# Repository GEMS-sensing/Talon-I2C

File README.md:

<!--  -->

# Talon-I2C
Talon daughterboard for [Flight data logger](https://github.com/GEMS-sensing/DFM_-_Flight?tab=readme-ov-file). Designed to interface with [Kestrel](https://github.com/GEMS-sensing/Project-Kestrel) main board. This board is designed to provide data logger with support to interface with I2C based sensors - a common interface for open source sensors.

# Repo Roadmap
#### [Documents](Documents/) 

General document and image storage for repo and README

#### [Hardware](Hardware/)

Current board files (Eagle), Bill of Materials (BoM), and other design documents

#### [Production](Production/)

Contains the various Gerber and pick and place files required to have the Printed Circuit Boards (PCBs) manufactured or populated 

#### [Software](Software/)

The software associated with the piece of hardware, this is usually diagnostic software used for verifying or investigating the hardware

<!-- #### [Mechanical](Mechanical/)

Mechanical design files and assembly documents -->

<!-- #### [Testing](Testing/)

Scripts and results from the testing process and development process. Contains more detailed information about documented issues among other testing. 
 -->

## Overview
* **Type:** Talon
* **Interfaces:** SDI-12
* **Release Version:** v2.1 - 2022/04/25

<!--  -->

## Features
### On-Board
* I2C ports (x4)
	* Isolated I2C bus for each port with line driver to deal with long, high capacitance sensor cables
* Port level current limit
	* Custom designed automatic current limit 
	* support for current and voltage measurement for each port
* Data and power control for each port
* Internal and external isolated I2C buses 
* EEPROM with UUID built in - can store additional values defined by firmware to track offsets, etc
* ESD protected inputs

<!-- ### Interface
* I<sup>2</sup>C
* M12 circular connector  -->

<!-- <picture>
  <source media="(prefers-color-scheme: dark)" srcset="Documents/Pinout_LIGHT.png">
  
</picture> -->

<!-- ## Specifications
* **Voltage - Supply:** 3.3V
* **Voltage - Logic:** 3.3V
* **Input Current (Avg, 1s period): 30.95&mu;A @ 3.3V**
* **Input Current (Avg, 5s period): 107.43&mu;A @ 3.3V**
* **Input Current (Max): 0.45mA @ 3.3V**

#### Sensor
**Temperature** [^1]
* Range: -40 ~ 125°C 
* Accuracy: &plusmn; 0.2°C
* Repeatability: &plusmn; 0.04°C

**Pressure** [^2]
* Range: 300 ~ 1200 hPa  
* Accuracy: &plusmn; 1 hPa
* Repeatability: &plusmn; 0.06 hPa

**Humidity** [^1]
* Range: 0 ~ 100%
* Accuracy: &plusmn; 2%
* Repeatability: 0.08%

[^1]: [SHT31 Datasheet](https://sensirion.com/media/documents/213E6A3B/63A5A569/Datasheet_SHT3x_DIS.pdf)
[^2]: [DPS368 Datasheet](https://www.infineon.com/dgdl/Infineon-DPS368-DS-v01_00-EN.pdf?fileId=5546d46269e1c019016a0c45105d4b40) -->

<!-- ## Version History

`v0.0` - Initial primal version with screw terminal

`v0.1` - Initial 'hard mount' version, using M12 connector

`v1.0` - Removed pullup select[^3], added logic level buffer and voltage reg on input

`v1.1` - Moved via away from connector pads to prevent bridging when soldering 

`v2.0` - Fixed issue with address select jumper[^3] -->

<!-- ## Jumper Settings 

> [!IMPORTANT]
> Jumper settings valid for version `v2.0` and beyond[^3]

[^3]: See Errata

**Configuration Jumpers**
| Jumper | Purpose | Open | Closed | Default | 
| ------ | ------- | ---------- | ---------- | ----- | 
| `JP1` | I<sup>2</sup>C Address Select | Base Address<sup>&dagger;</sup> | Alt Address<sup>&Dagger;</sup> | Open |

&dagger; SHT31 = `0x44`, DPS368 = `0x76`

&Dagger; SHT31 = `0x44`, DPS368 = `0x77`
 -->

## Known Issues/Errata

None
<!-- #### Solder Jumper Stencil

**Version Affected:** All

**Issue:** Solar input does not support very low impedance sources (e.g. lead acid battery) - see details in issue [#20](https://github.com/GEMS-sensing/Project-Kestrel/issues/20)

**Workaround:** 

* Avoid use of low impedance batteries for input
* Include series impedance to prevent current spikes (not desirable)
* Perform board patch described in issue [#20](https://github.com/GEMS-sensing/Project-Kestrel/issues/20) -->

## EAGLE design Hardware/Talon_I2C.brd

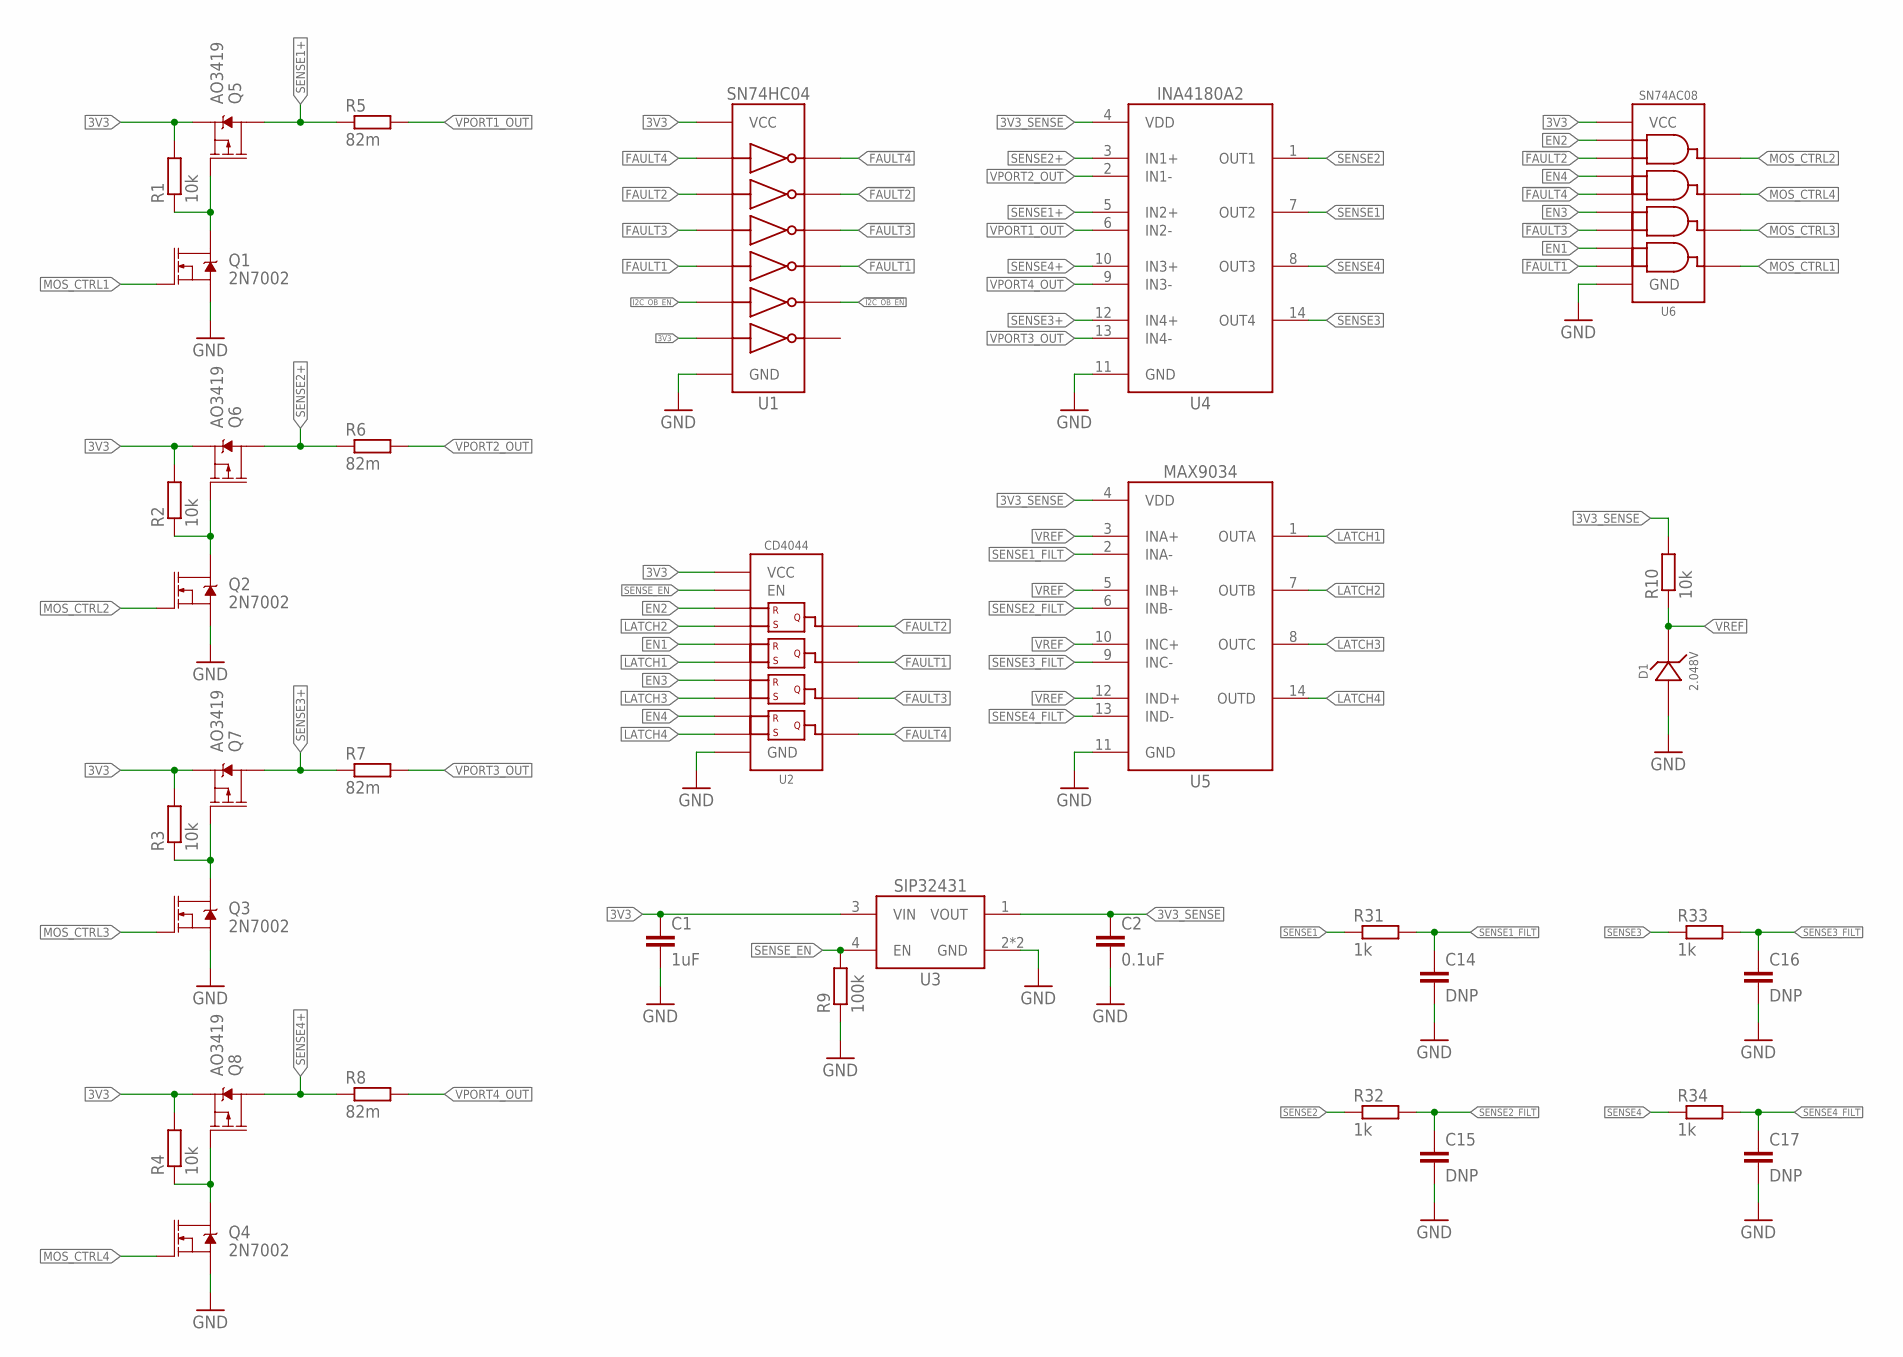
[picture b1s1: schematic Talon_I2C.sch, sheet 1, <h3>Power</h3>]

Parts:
C1: 1uF; C0603
C2: 0.1uF; C0402
C14, C15, C16, C17: DNP; C0402; MPN DNP; DIGIKEY DNP
D1: 2.048V; SOT23-3
Q1, Q2, Q3, Q4: 2N7002; SOT23-3
Q5, Q6, Q7, Q8: AO3419; SOT23-3
R1, R2, R3, R4, R10: 10k; R0402
R5, R6, R7, R8: 82m; R0603
R9: 100k; R0402
R31, R32, R33, R34: 1k; R0402
U1: SN74HC04; TSSOP14
U2: CD4044; TSSOP16
U3: SIP32431TDFN; TDFN_4
U4: INA4180A2; TSSOP14
U5: MAX9034TSSOP; TSSOP14
U6: SN74AC08; TSSOP14

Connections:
3V3: C1.1, Q5.2 (S), Q6.2 (S), Q7.2 (S), Q8.2 (S), R1.2, R2.2, R3.2, R4.2, U1.13 (A6), U1.14 (VCC), U2.16 (VCC), U3.3 (VIN), U6.14 (VCC); also elsewhere on the board
3V3_SENSE: C2.1, R10.2, U3.1 (VOUT), U4.4 (VDD), U5.4 (VDD)
!FAULT1: U1.8 (Y4), U6.13 (B4)
!FAULT2: U1.4 (Y2), U6.2 (B1)
!FAULT3: U1.6 (Y3), U6.10 (B3)
!FAULT4: U1.2 (Y1), U6.5 (B2)
!I2C_OB_EN: U1.10 (Y5); also elsewhere on the board
EN1: U2.6 (R2), U6.12 (A4); also elsewhere on the board
EN2: U2.4 (R1), U6.1 (A1); also elsewhere on the board
EN3: U2.12 (R3), U6.9 (A3); also elsewhere on the board
EN4: U2.14 (R4), U6.4 (A2); also elsewhere on the board
FAULT1: U1.9 (A4), U2.9 (Q2); also elsewhere on the board
FAULT2: U1.3 (A2), U2.13 (Q1); also elsewhere on the board
FAULT3: U1.5 (A3), U2.10 (Q3); also elsewhere on the board
FAULT4: U1.1 (A1), U2.1 (Q4); also elsewhere on the board
GND: C1.2, C2.2, C14.2, C15.2, C16.2, C17.2, D1.2 (A), Q1.2 (S), Q2.2 (S), Q3.2 (S), Q4.2 (S), R9.1, U1.7 (GND), U2.8 (GND), U3.2 (GND), U3.EP (GND), U4.11 (GND), U5.11 (GND), U6.7 (GND); also elsewhere on the board
I2C_OB_EN: U1.11 (A5); also elsewhere on the board
LATCH1: U2.7 (S2), U5.1 (OUTA)
LATCH2: U2.3 (S1), U5.7 (OUTB)
LATCH3: U2.11 (S3), U5.8 (OUTC)
LATCH4: U2.15 (S4), U5.14 (OUTD)
MOS_CTRL1: Q1.1 (G), U6.11 (Y4)
MOS_CTRL2: Q2.1 (G), U6.3 (Y1)
MOS_CTRL3: Q3.1 (G), U6.8 (Y3)
MOS_CTRL4: Q4.1 (G), U6.6 (Y2)
unnamed: Q2.3 (D), Q6.1 (G), R2.1
unnamed: Q1.3 (D), Q5.1 (G), R1.1
unnamed: Q3.3 (D), Q7.1 (G), R3.1
unnamed: Q4.3 (D), Q8.1 (G), R4.1
SENSE1: R31.1, U4.7 (OUT2); also elsewhere on the board
SENSE1+: Q5.3 (D), R5.1, U4.5 (IN2+)
SENSE1_FILT: C14.1, R31.2, U5.2 (INA-)
SENSE2: R32.1, U4.1 (OUT1); also elsewhere on the board
SENSE2+: Q6.3 (D), R6.1, U4.3 (IN1+)
SENSE2_FILT: C15.1, R32.2, U5.6 (INB-)
SENSE3: R33.1, U4.14 (OUT4); also elsewhere on the board
SENSE3+: Q7.3 (D), R7.1, U4.12 (IN4+)
SENSE3_FILT: C16.1, R33.2, U5.9 (INC-)
SENSE4: R34.1, U4.8 (OUT3); also elsewhere on the board
SENSE4+: Q8.3 (D), R8.1, U4.10 (IN3+)
SENSE4_FILT: C17.1, R34.2, U5.13 (IND-)
SENSE_EN: R9.2, U2.5 (EN), U3.4 (EN); also elsewhere on the board
VPORT1_OUT: R5.2, U4.6 (IN2-); also elsewhere on the board
VPORT2_OUT: R6.2, U4.2 (IN1-); also elsewhere on the board
VPORT3_OUT: R7.2, U4.13 (IN4-); also elsewhere on the board
VPORT4_OUT: R8.2, U4.9 (IN3-); also elsewhere on the board
VREF: D1.1 (C), R10.1, U5.3 (INA+), U5.5 (INB+), U5.10 (INC+), U5.12 (IND+)

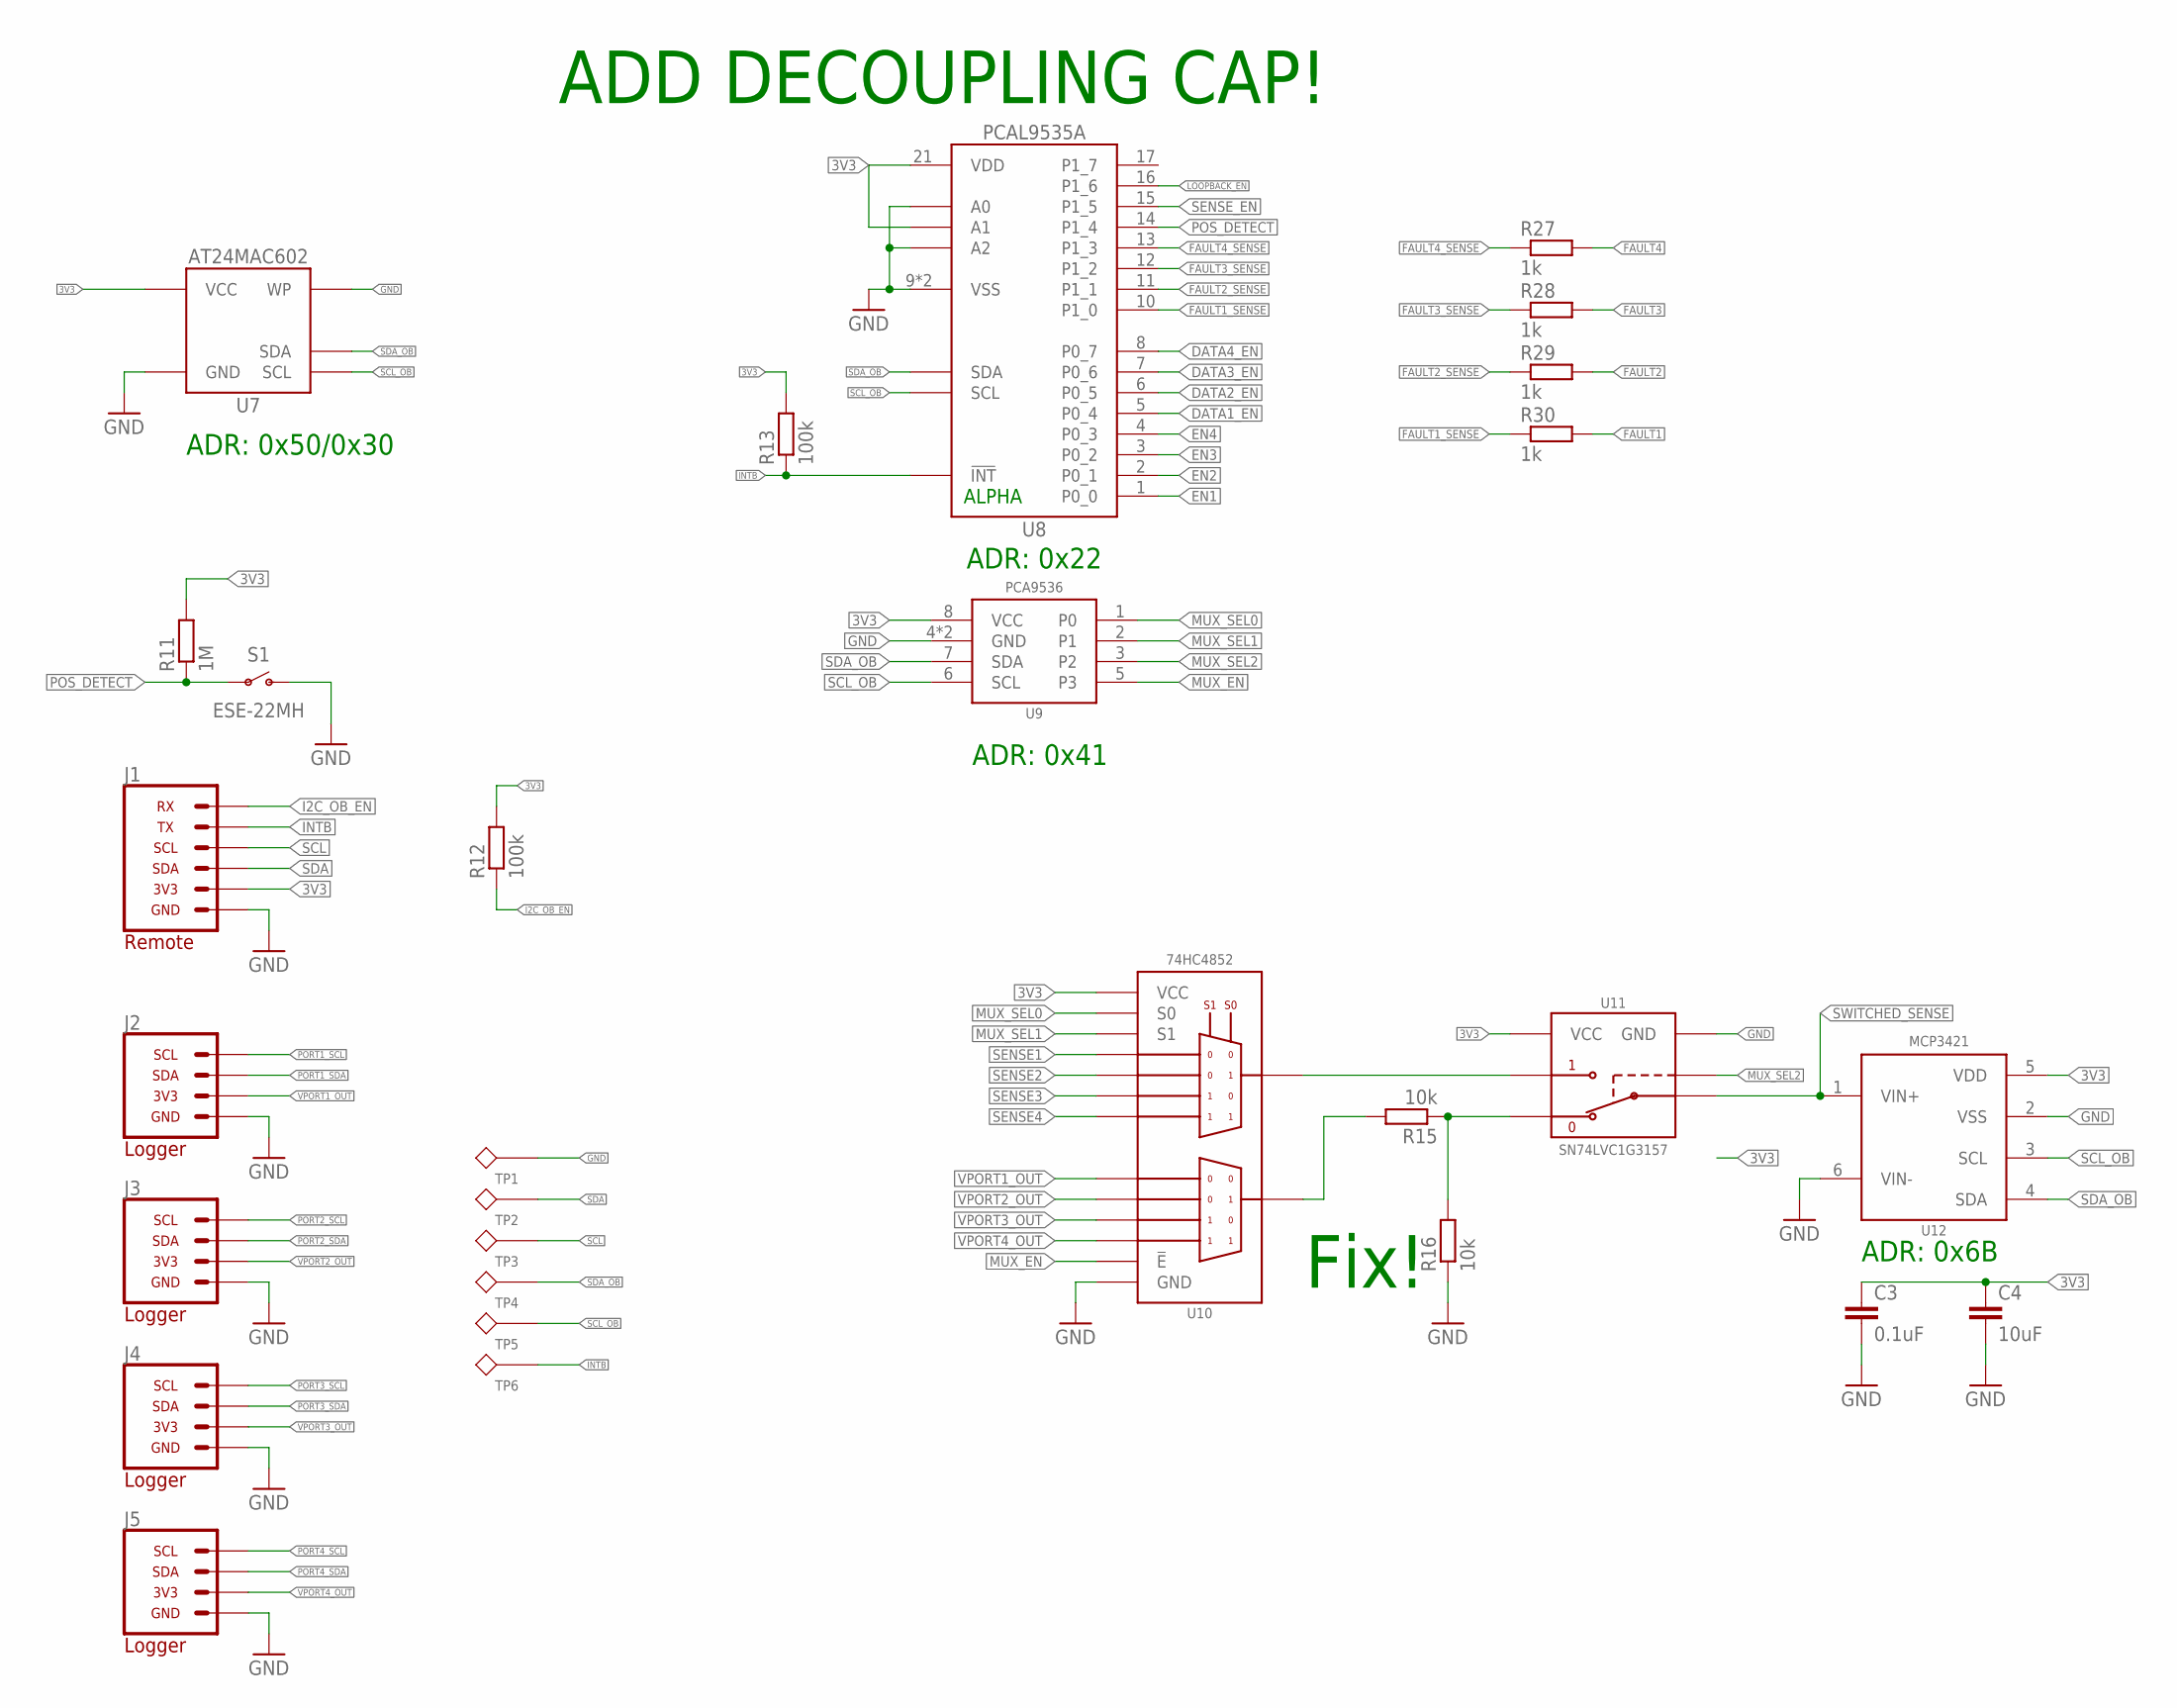
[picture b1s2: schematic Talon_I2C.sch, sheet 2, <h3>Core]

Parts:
C3: 0.1uF; C0402
C4: 10uF; C0805
J1: CONN_TALON_REMOTE; 1X06_MICROLOCKPLUS
J2, J3, J4, J5: CONN_I2C_LOGGER; 1X04_M8_TE_T404103_BOARDLOCK
R11: 1M; R0402
R12, R13: 100k; R0402
R15, R16: 10k; R0402
R27, R28, R29, R30: 1k; R0402
S1: ESE-22MH
TP1, TP2, TP3, TP4, TP5, TP6: TESTPOINTRCU; TESTPOINT_0603
U7: AT24MAC602SOT23; SOT23-5
U8: PCAL9535AQFN; QFN24
U9: PCA9536DFN; DFN_8_3X3
U10: 74HC4852; VQFN-16
U11: SN74LVC1G3157SC70; DCK_R-PDSO-G6
U12: MCP3421A3; SOT23-6L

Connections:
3V3: C3.1, C4.1, J1.2 (3V3), R11.2, R12.2, R13.2, U7.4 (VCC), U8.21 (VDD), U8.23 (A1), U9.8 (VCC), U10.16 (VCC), U11.5 (VCC), U12.5 (VDD); also elsewhere on the board
DATA1_EN: U8.5 (P0_4); also elsewhere on the board
DATA2_EN: U8.6 (P0_5); also elsewhere on the board
DATA3_EN: U8.7 (P0_6); also elsewhere on the board
DATA4_EN: U8.8 (P0_7); also elsewhere on the board
EN1: U8.1 (P0_0); also elsewhere on the board
EN2: U8.2 (P0_1); also elsewhere on the board
EN3: U8.3 (P0_2); also elsewhere on the board
EN4: U8.4 (P0_3); also elsewhere on the board
FAULT1: R30.2; also elsewhere on the board
FAULT1_SENSE: R30.1, U8.10 (P1_0)
FAULT2: R29.2; also elsewhere on the board
FAULT2_SENSE: R29.1, U8.11 (P1_1)
FAULT3: R28.2; also elsewhere on the board
FAULT3_SENSE: R28.1, U8.12 (P1_2)
FAULT4: R27.2; also elsewhere on the board
FAULT4_SENSE: R27.1, U8.13 (P1_3)
GND: C3.2, C4.2, J1.1 (GND), J2.4 (GND), J3.4 (GND), J4.4 (GND), J5.4 (GND), R16.1, S1.1 (O), TP1.1, U7.2 (GND), U7.5 (WP), U8.9 (VSS), U8.18 (A0), U8.24 (A2), U8.EP (VSS), U9.4 (GND), U9.EP (GND), U10.8 (GND), U10.EP (GND), U11.2 (GND), U12.2 (VSS), U12.6 (VIN-); also elsewhere on the board
I2C_OB_EN: J1.6 (RX), R12.1; also elsewhere on the board
INTB: J1.5 (TX), R13.1, TP6.1, U8.22 (!INT)
LOOPBACK_EN: U8.16 (P1_6); also elsewhere on the board
MUX_EN: U9.5 (P3), U10.6 (!E)
MUX_SEL0: U9.1 (P0), U10.10 (S0)
MUX_SEL1: U9.2 (P1), U10.9 (S1)
MUX_SEL2: U9.3 (P2), U11.6 (S)
unnamed: R15.2, U10.3 (2Z)
unnamed: R15.1, R16.2, U11.3 (B1)
unnamed: U10.13 (1Z), U11.1 (B2)
PORT1_SCL: J2.3 (SCL); also elsewhere on the board
PORT1_SDA: J2.1 (SDA); also elsewhere on the board
PORT2_SCL: J3.3 (SCL); also elsewhere on the board
PORT2_SDA: J3.1 (SDA); also elsewhere on the board
PORT3_SCL: J4.3 (SCL); also elsewhere on the board
PORT3_SDA: J4.1 (SDA); also elsewhere on the board
PORT4_SCL: J5.3 (SCL); also elsewhere on the board
PORT4_SDA: J5.1 (SDA); also elsewhere on the board
POS_DETECT: R11.1, S1.2, U8.14 (P1_4)
SCL: J1.4 (SCL), TP3.1; also elsewhere on the board
SCL_OB: TP5.1, U7.1 (SCL), U8.19 (SCL), U9.6 (SCL), U12.3 (SCL); also elsewhere on the board
SDA: J1.3 (SDA), TP2.1; also elsewhere on the board
SDA_OB: TP4.1, U7.3 (SDA), U8.20 (SDA), U9.7 (SDA), U12.4 (SDA); also elsewhere on the board
SENSE1: U10.12 (1Y0); also elsewhere on the board
SENSE2: U10.14 (1Y1); also elsewhere on the board
SENSE3: U10.15 (1Y2); also elsewhere on the board
SENSE4: U10.11 (1Y3); also elsewhere on the board
SENSE_EN: U8.15 (P1_5); also elsewhere on the board
SWITCHED_SENSE: U11.4 (A), U12.1 (VIN+)
VPORT1_OUT: J2.2 (3V3), U10.1 (2Y0); also elsewhere on the board
VPORT2_OUT: J3.2 (3V3), U10.5 (2Y1); also elsewhere on the board
VPORT3_OUT: J4.2 (3V3), U10.2 (2Y2); also elsewhere on the board
VPORT4_OUT: J5.2 (3V3), U10.4 (2Y3); also elsewhere on the board

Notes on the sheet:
ALPHA
ADD DECOUPLING CAP!
Fix!
ADR: 0x22
ADR: 0x6B
ADR: 0x50/0x30
ADR: 0x41

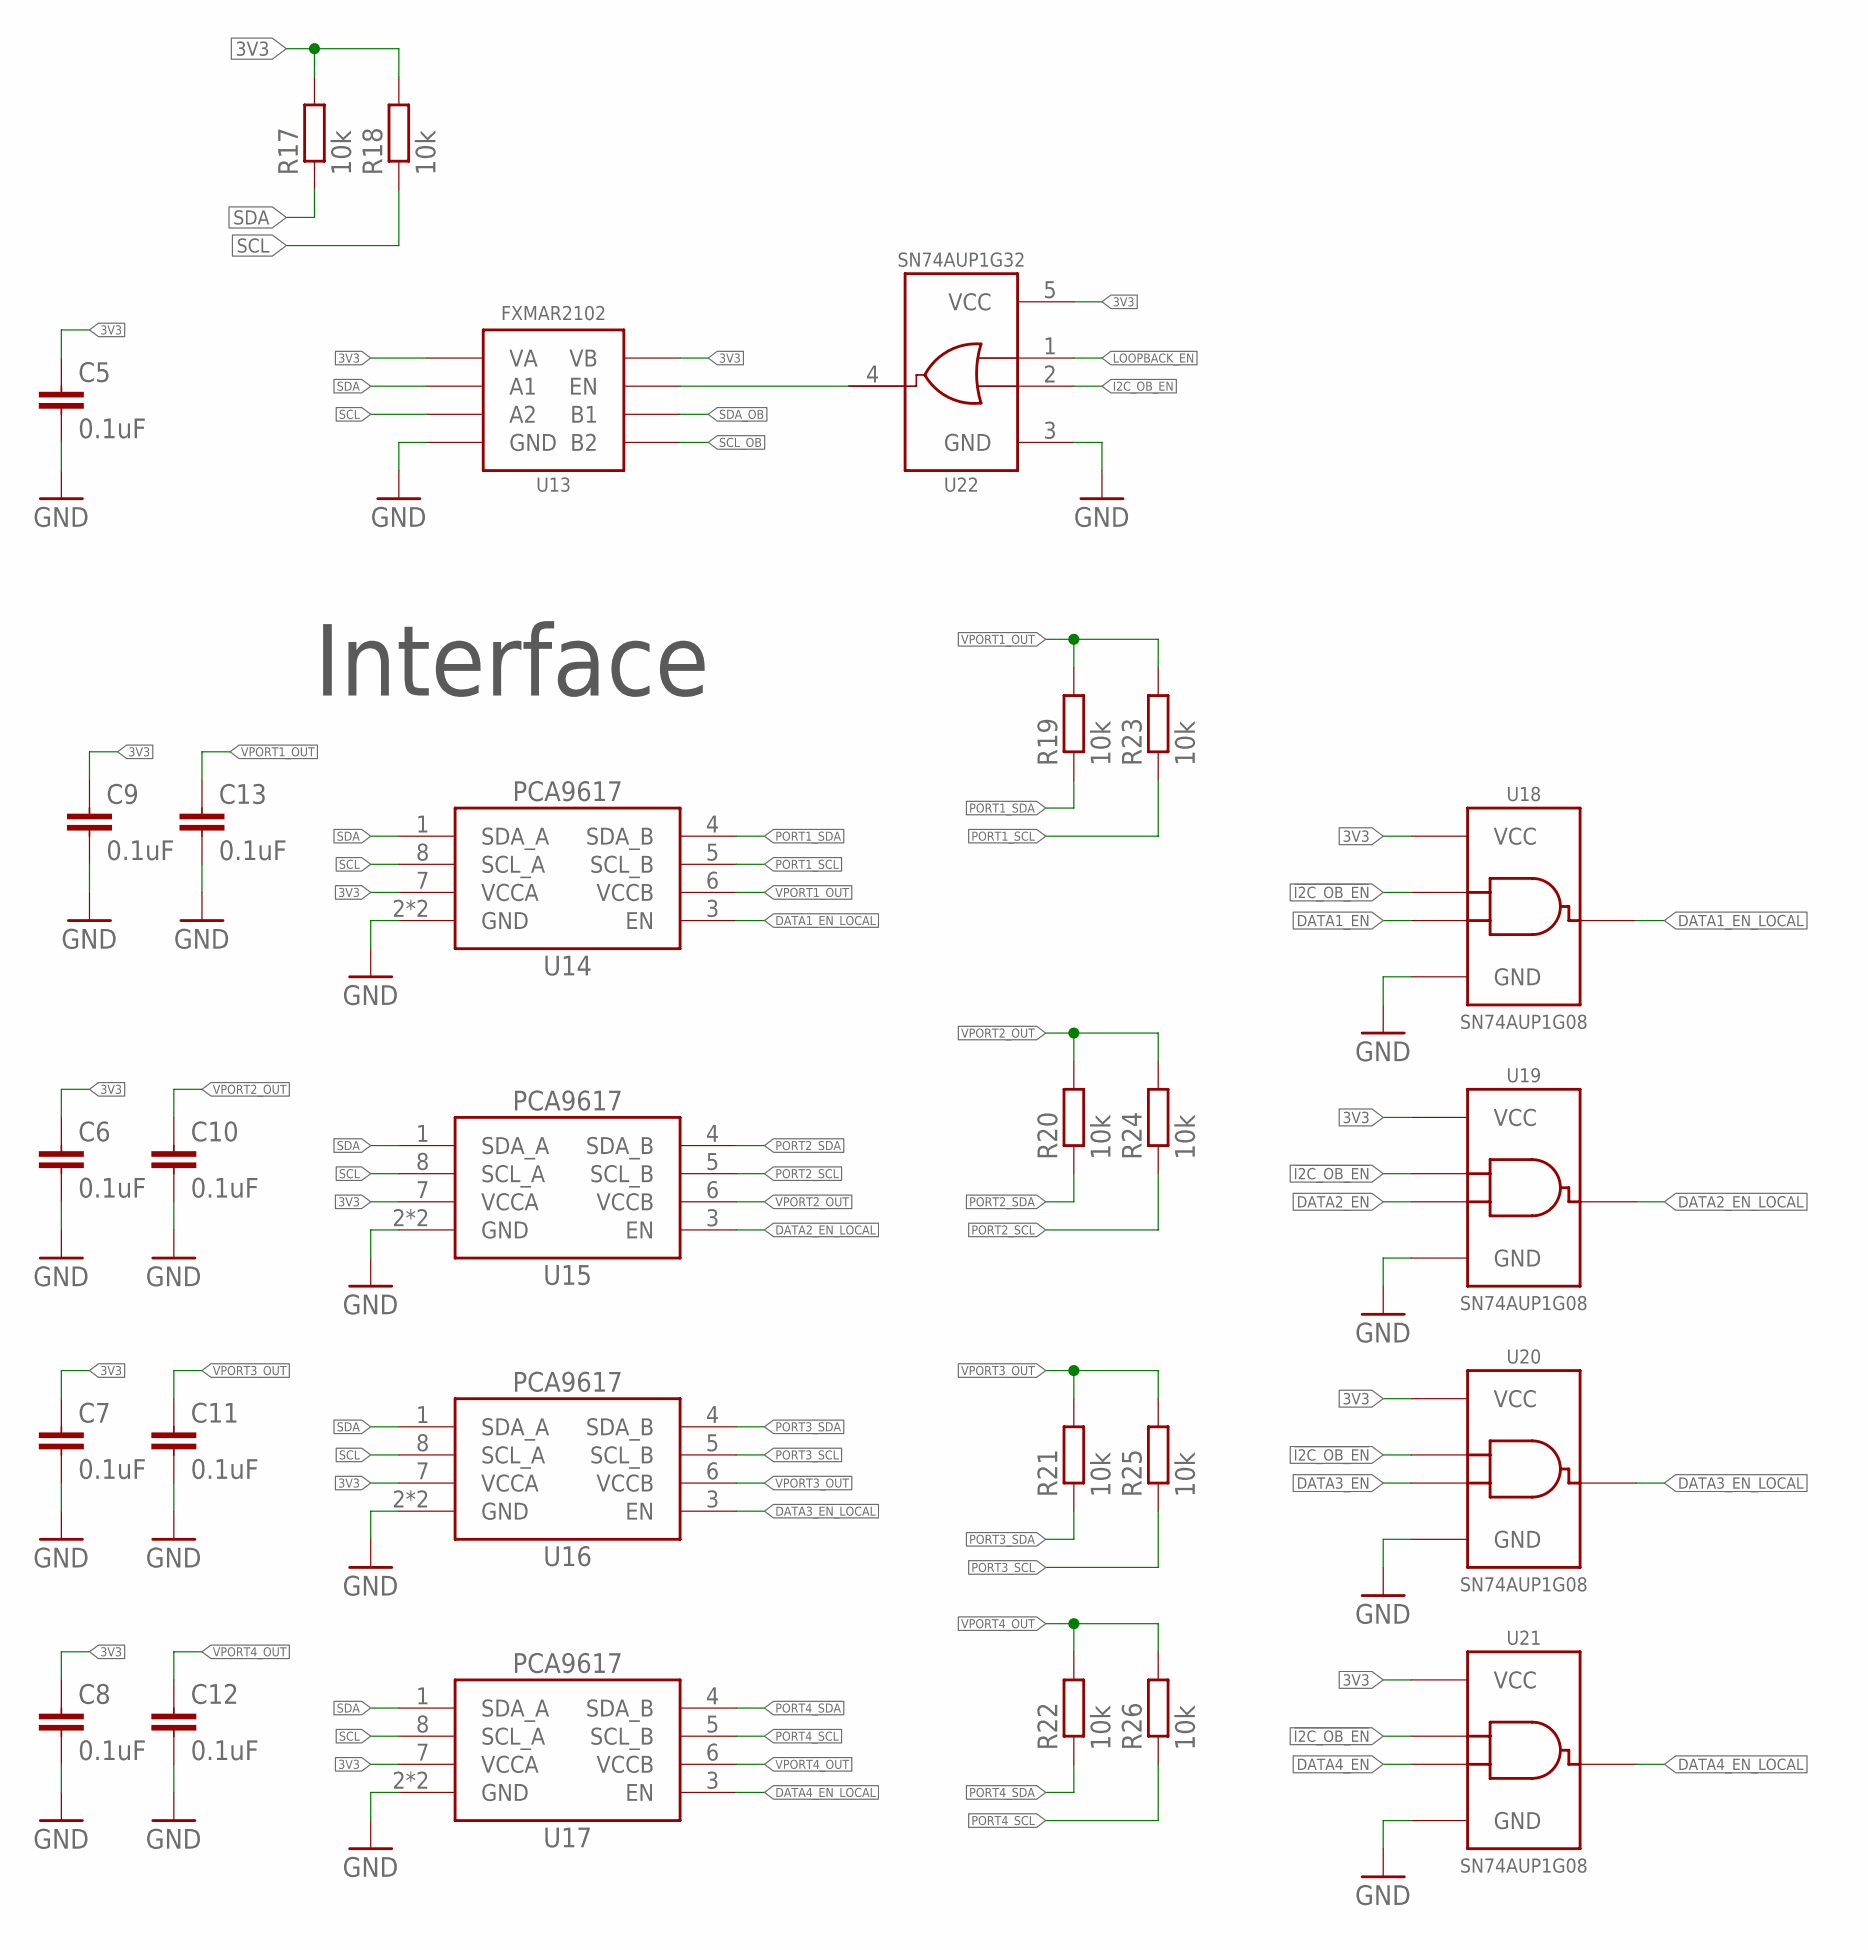
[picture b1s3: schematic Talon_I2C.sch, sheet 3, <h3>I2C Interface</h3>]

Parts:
C5, C6, C7, C8, C9, C10, C11, C12, C13: 0.1uF; C0402
R17, R18, R19, R20, R21, R22, R23, R24, R25, R26: 10k; R0402
U13: FXMAR2102UMLP; UQFN-8_1.4X1.2
U14, U15, U16, U17: PCA9617WSON; WSON-8_2X3
U18, U19, U20, U21: SN74AUP1G08DCK; DCK_R-PDSO-G5
U22: SN74AUP1G32DCK; DCK_R-PDSO-G5

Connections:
3V3: C5.1, C6.1, C7.1, C8.1, C9.1, R17.2, R18.2, U13.1 (VA), U13.8 (VB), U14.7 (VCCA), U15.7 (VCCA), U16.7 (VCCA), U17.7 (VCCA), U18.5 (VCC), U19.5 (VCC), U20.5 (VCC), U21.5 (VCC), U22.5 (VCC); also elsewhere on the board
!I2C_OB_EN: U18.1 (A), U19.1 (A), U20.1 (A), U21.1 (A); also elsewhere on the board
DATA1_EN: U18.2 (B); also elsewhere on the board
DATA1_EN_LOCAL: U14.3 (EN), U18.4 (Y)
DATA2_EN: U19.2 (B); also elsewhere on the board
DATA2_EN_LOCAL: U15.3 (EN), U19.4 (Y)
DATA3_EN: U20.2 (B); also elsewhere on the board
DATA3_EN_LOCAL: U16.3 (EN), U20.4 (Y)
DATA4_EN: U21.2 (B); also elsewhere on the board
DATA4_EN_LOCAL: U17.3 (EN), U21.4 (Y)
GND: C5.2, C6.2, C7.2, C8.2, C9.2, C10.2, C11.2, C12.2, C13.2, U13.4 (GND), U14.2 (GND), U14.EP (GND), U15.2 (GND), U15.EP (GND), U16.2 (GND), U16.EP (GND), U17.2 (GND), U17.EP (GND), U18.3 (GND), U19.3 (GND), U20.3 (GND), U21.3 (GND), U22.3 (GND); also elsewhere on the board
I2C_OB_EN: U22.2 (B); also elsewhere on the board
LOOPBACK_EN: U22.1 (A); also elsewhere on the board
unnamed: U13.5 (EN), U22.4 (Y)
PORT1_SCL: R23.1, U14.5 (SCL_B); also elsewhere on the board
PORT1_SDA: R19.1, U14.4 (SDA_B); also elsewhere on the board
PORT2_SCL: R24.1, U15.5 (SCL_B); also elsewhere on the board
PORT2_SDA: R20.1, U15.4 (SDA_B); also elsewhere on the board
PORT3_SCL: R25.1, U16.5 (SCL_B); also elsewhere on the board
PORT3_SDA: R21.1, U16.4 (SDA_B); also elsewhere on the board
PORT4_SCL: R26.1, U17.5 (SCL_B); also elsewhere on the board
PORT4_SDA: R22.1, U17.4 (SDA_B); also elsewhere on the board
SCL: R18.1, U13.3 (A2), U14.8 (SCL_A), U15.8 (SCL_A), U16.8 (SCL_A), U17.8 (SCL_A); also elsewhere on the board
SCL_OB: U13.6 (B2); also elsewhere on the board
SDA: R17.1, U13.2 (A1), U14.1 (SDA_A), U15.1 (SDA_A), U16.1 (SDA_A), U17.1 (SDA_A); also elsewhere on the board
SDA_OB: U13.7 (B1); also elsewhere on the board
VPORT1_OUT: C13.1, R19.2, R23.2, U14.6 (VCCB); also elsewhere on the board
VPORT2_OUT: C10.1, R20.2, R24.2, U15.6 (VCCB); also elsewhere on the board
VPORT3_OUT: C11.1, R21.2, R25.2, U16.6 (VCCB); also elsewhere on the board
VPORT4_OUT: C12.1, R22.2, R26.2, U17.6 (VCCB); also elsewhere on the board

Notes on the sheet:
Interface

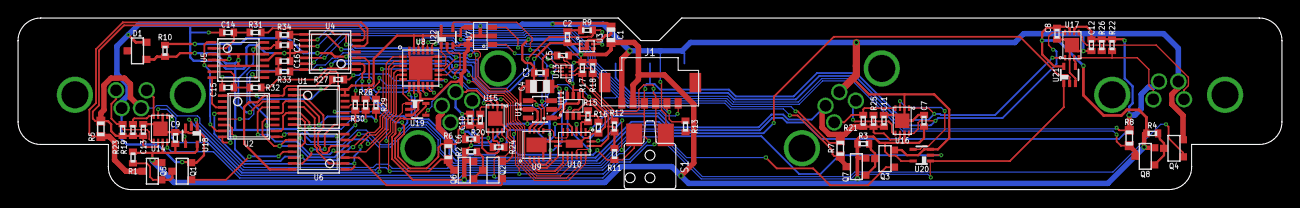
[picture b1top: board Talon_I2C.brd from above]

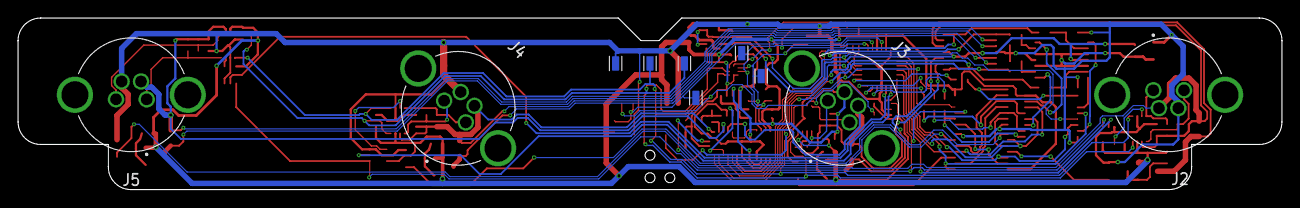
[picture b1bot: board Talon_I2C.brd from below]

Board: 2 copper layers, 140.0 x 19.0 mm, 93 parts (10 on the bottom side), 83 nets.

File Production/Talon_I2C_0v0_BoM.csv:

"Qty","Value","Device","Package","Parts","Description","DIGIKEY","DISP","MF","MOUSER","MPN","VALUE","VALUE_PART",
"11","0.1uF","C-EU0.1UFC0402","C0402","C2, C3, C5, C6, C7, C8, C9, C10, C11, C12, C13","CAPACITOR, European symbol","490-4759-1-ND","","Murata","","GCM155R71C104KA55D","","",
"2","100k","R-EU_100KR0402","R0402","R9, R12","RESISTOR, European symbol","311-100KLRCT-ND","","Yageo","","RC0402FR-07100KL","","100k",
"17","10k","R-EU_10KR0402","R0402","R1, R2, R3, R4, R10, R15, R16, R17, R18, R19, R20, R21, R22, R23, R24, R25, R26","RESISTOR, European symbol","311-10.0KLRCT-ND","","Yageo","","RC0402FR-0710KL","","10k",
"1","10uF","C-EU10UFC0805","C0805","C4","CAPACITOR, European symbol","490-6473-1-ND","","Murata","","GRM21BR61C106KE15K","","",
"1","110k","R-EU_110KR0603","R0603","R13","RESISTOR, European symbol","CR0603-FX-1103ELFCT-ND","","Bourns","","CR0603-FX-1103ELF","","110k",
"1","1M","R-EU_1MR0402","R0402","R11","RESISTOR, European symbol","311-1.00MLRCT-ND","","Yageo","","RC0402FR-071ML","","1M",
"1","1uF","C-EU1UFC0603","C0603","C1","CAPACITOR, European symbol","587-1251-1-ND","","Yaiyo Yuden","","EMK107BJ105KA-T","","",
"1","2.048V","LM40402.048","SOT23-3","D1","LM4040 - Precision Micropower Shunt Voltage Referance","LM4040CIM3-2.0/NOPBCT-ND","","TI","","LM4040CIM3-2.0/NOPB","","",
"1","24AA02SOT23","24AA02SOT23","SOT23-5","U7","24AA02 - 2k I2C Serial EEPROM","24AA025E64T-I/OTCT-ND","24AA025E64","Microchip","24AA025E64T-I/OTCT-ND","24AA025E64T-I/OT","","",
"4","2N7002","MOSFET-NCH-2N7002P","SOT23-3","Q1, Q2, Q3, Q4","N-channel MOSFET","1727-4692-1-ND","","Nexperia","","2N7002P","215","2N7002",
"1","49.9k","R-EU_49.9KR0603","R0603","R14","RESISTOR, European symbol","RMCF0603FG49K9CT-ND","","Stackpole","","RMCF0603FG49K9","","49.9k",
"1","74HC4852","74HC4852","VQFN-16","U10","74HC4852  - Analog Multiplexer, Dual 4-Channel (1:4 x 2)","1727-7953-1-ND","74HC4852","Nexperia","","74HC4852BQ-Q100","11","",
"4","82m","R-EU_0.082R0603","R0603","R5, R6, R7, R8","RESISTOR, European symbol","408-1446-1-ND","","Susumu","","RL0816T-R082-F","","82m",
"4","AO3419","MOSFET-PCH-AO3419","SOT23-3","Q5, Q6, Q7, Q8","P-channel MOSFET","785-1013-1-ND","","Alpha and Omega","","AO3419","AO3419","",
"1","CD4044","CD4044","TSSOP16","U2","CD404x  - S-R Latch, Quad","296-31499-1-ND","CD4044","TI","","CD4044BPWR","","",
"4","CONN_I2C_LOGGER","CONN_I2C_LOGGER","1X04_M8_TE_T404103_BOARDLOCK","J2, J3, J4, J5","GEMS Connector for I2C Devices - Logger Side","A126815-ND","Logger","TE","","T4041037041-000","","",
"1","CONN_TALON_REMOTE","CONN_TALON_REMOTE","1X06_MICROLOCKPLUS","J1","GEMS Connector for Talon Interface","900-2059570671CT-ND","Remote","Molex","","2059570671","","",
"1","ESE-22MH","SPSTESE-22MH","ESE-22MH","S1","Generic SPST (Single Pole Single Throw) Switch","P13584SCT-ND","","Panasonic","","ESE-22MH24","ESE-22MH","",
"1","FXMAR2102UMLP","FXMAR2102UMLP","UQFN-8_1.4X1.2","U13","FXMAR2102 - 2 Channel Bidirectional Voltage Level Translator for I2C Applications","FXMAR2102UMX-F106CT-ND","FXMAR2102","OnSemi","","FXMAR2102UMX-F106","","",
"1","INA4180A2","INA4180A2","TSSOP14","U4","INA4180 - Analog Output Current Sense Amplifier","296-49095-1-ND","INA4180A2","TI","","INA4180A2IPWR","","",
"1","MAX9034TSSOP","MAX9034TSSOP","TSSOP14","U5","MAX9034 - Ultra-Small nanoPower Single Comparator , Quad","MAX9034AUD+CT-ND","MAX9034","Maxim","","MAX9034AUD+T","","",
"1","MCP23018QFN","MCP23018QFN","QFN24","U8","MCP23018 - I2C I/O Expander, 16 bit wtih interrupt and reset","MCP23018T-E/MJCT-ND","","TI","","MCP23018T-E/MJ","","",
"1","MCP3421A3","MCP3421A3","SOT23-6L","U12","MCP342* - Sigma Delta ADC","MCP3421A3T-E/CHCT-ND","MCP3421","Microchip","","MCP3421A3T-E/CH","","",
"1","PCA9536DFN","PCA9536DFN","DFN_8_3X3","U9","PCA9536 - I2C I/O Expander, 4 bit, 5V tollerant","568-4079-1-ND","","NXP","","PCA9536TK","118","",
"4","PCA9617WSON","PCA9617WSON","WSON-8_2X3","U14, U15, U16, U17","PCA9617A - Level translating I2C Bus Repeater","568-10953-1-ND","","NXP","","PCA9617ATPZ","","",
"1","SIP32431TDFN","SIP32431TDFN","TDFN_4","U3","SiP3243x - Ultra Low Leakage Load Switch with Reverse Blocking","SIP32431DNP3-T1GE4CT-ND","SIP32431","Vishay","","SIP32431DNP3-T1GE4","","",
"1","SN74AC08","SN74AC08","TSSOP14","U6","SN74AC08 - AND, 4 Element, 2 Input","296-4292-1-ND","","TI","","SN74AC08PWR","","",
"4","SN74AUP1G08DCK","SN74AUP1G08DCK","DCK_R-PDSO-G5","U18, U19, U20, U21","SN74AUP1G08 - AND, 1 Element, 2 Input","296-19075-1-ND","","TI","","SN74AUP1G08DCKR","","",
"1","SN74AUP1T157DCK","SN74AUP1T157DCK","DCK_R-PDSO-G6","U11","SN74AUP1T157  - Non-Inverting Digital Multiplexer, Schmitt Trigger (1:2)","296-27393-1-ND","SN74AUP1T157","TI","","SN74AUP1T157DCKR","","",
"1","SN74HC04","SN74HC04","TSSOP14","U1","SN74HC04 - NOT, 4 Element, 1 Input - Hex Inverter","296-8208-1-ND","","TI","","SN74HC04PWR","","",
"6","TESTPOINTRCU","TESTPOINTRCU","TESTPOINT_0603","TP1, TP2, TP3, TP4, TP5, TP6","Test Point","A106145CT-ND","","TE Connectivity","","RCU-0C","","",

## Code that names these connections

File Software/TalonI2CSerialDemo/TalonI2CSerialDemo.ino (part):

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const uint8_t Dir = 0;

//IO Expander pins
const uint8_t POS_DETECT = 12; 
const uint8_t SENSE_EN = 13;

//IO Sense pins
const uint8_t MUX_EN = 3;
const uint8_t MUX_SEL0 = 0;
const uint8_t MUX_SEL1 = 1;
const uint8_t MUX_SEL2 = 2;

const float VoltageDiv = 3; //Program voltage divider
const float CurrentDiv = 0.243902439; //82mOhm, 50V/V Amp
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		io.pinMode(i, INPUT_PULLUP);
	}

	io.pinMode(POS_DETECT, INPUT); //Set position detect as normal pullup (has external pullup)
	io.pinMode(SENSE_EN, OUTPUT); //Set sense control as output
	io.digitalWrite(SENSE_EN, HIGH); //Default sense to on 
	digitalWrite(I2C_EN, HIGH); //Turn on external I2C
}
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
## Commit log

2021-10-07 Initial design via copy from SDI-12 Talon
    Added the initial design as a copy from the SDI-12 Talon in order to utilize the existing layout of the current limit sub-circuit, etc
2021-10-08 Copper layout done
2021-10-08 Generated gerbers for v0.0
    Ready for final review
2021-10-12 Layout, gerbers and BoM for v0.0 - submitted to fab
2021-10-14 Generated documentation for v0.1 quote - NAMING ERROR
    Note: These documents reflect the changes made fro v0.0 -> v0.1, but the marking on the board was not updated, so it still reads v0.0, despite being updated from the original version.
2021-10-14 Fixed board silkscreen issue - NAMING ERROR
    Corrected the naming error on the board and generated new gerbers
2021-10-21 Added alpha test firmware
2021-11-17 Minor demo updates
2021-11-22 Updates for v1.0, sent to fab
    Made fixes for v1.0:
    - Fixed bypass control
    - Added filter lines (clitch protection) to sense lines
    - Flipped Talon connector port pinout
    - Moved MUX (U9/U10) to prevent soldering issues
    - Moved U6 to prevent bumping
2021-11-22 Updated paste for v1.0
2021-11-23 v1.1 updates
    Moved port 1 and port 4, sent to fab
2021-12-09 Add dimension drawings
2021-12-09 Add BoM for v1.1
2021-12-09 Add mechanical files for v1.1
2021-12-10 v2.0 update
    Fixed physical overlap in current limit circuit, fixed connector pinout
2022-03-30 Added license
2022-04-06 Part number updates
2022-04-22 Updated EEPROM part
2022-04-25 v2.1 updates
    Updates made to schematic and layout, boards sent to fab
2024-09-01 Updated README and board images
2024-11-02 Added production info

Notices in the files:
parts and their libraries:
bschulz: This work is licensed under the Creative Commons Attribution-ShareAlike 4.0
http://creativecommons.org/licenses/by-sa/4.0
